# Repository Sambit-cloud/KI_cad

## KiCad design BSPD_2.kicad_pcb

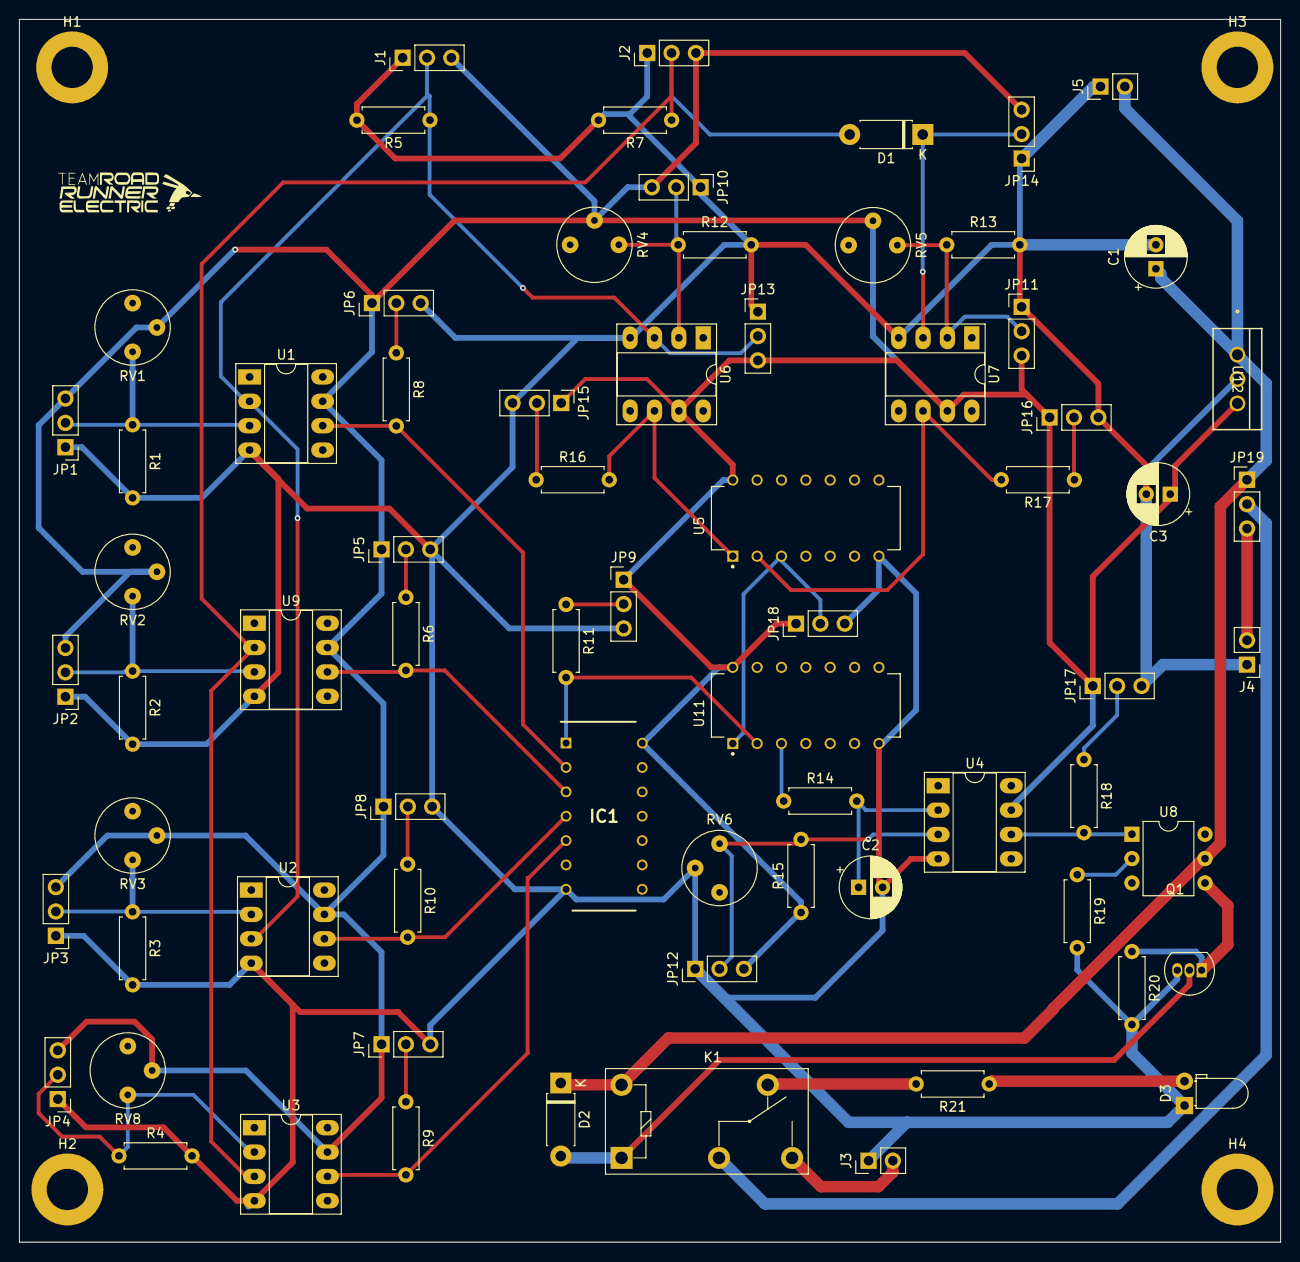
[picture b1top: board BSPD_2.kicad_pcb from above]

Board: 2 copper layers, 131.5 x 127.5 mm, 76 parts (0 on the bottom side), 40 nets.

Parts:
C1: 0.33u; CP_Radial_D6.3mm_P2.50mm
C2: 330u; CP_Radial_D6.3mm_P2.50mm
C3: 0.1u; CP_Radial_D6.3mm_P2.50mm
D1, D2: D; D_DO-41_SOD81_P7.62mm_Horizontal
D3: LED; LED_D3.0mm_Horizontal_O1.27mm_Z6.0mm
H1, H2, H3, H4: M4; MountingHole_4.3mm_M4_DIN965_Pad
IC1: CD4072BE; DIP794W53P254L1930H508Q14N
J1: BrakePressure_Sens_Input; PinHeader_1x03_P2.54mm_Vertical
J2: Current_Sensor_Input; PinHeader_1x03_P2.54mm_Vertical
J3: BSPD_Output; PinHeader_1x02_P2.54mm_Vertical
J4: Shutdown Line; PinHeader_1x02_P2.54mm_Vertical
J5: Voltage_Input; PinHeader_1x02_P2.54mm_Vertical
JP1, JP2, JP3, JP4, JP5, JP6, JP7, JP8, JP9, JP10, JP11, JP12, JP13, JP14, JP15, JP16, JP17, JP18, JP19: Jumper_3_Open; PinHeader_1x03_P2.54mm_Vertical
K1: G5Q-1; Relay_SPDT_Omron-G5Q-1
Q1: Q_NMOS_DGS; TO-92_Inline
R1, R14, R20: 1k; R_Axial_DIN0207_L6.3mm_D2.5mm_P7.62mm_Horizontal
R2, R4: 34k; R_Axial_DIN0207_L6.3mm_D2.5mm_P7.62mm_Horizontal
R3: 9k; R_Axial_DIN0207_L6.3mm_D2.5mm_P7.62mm_Horizontal
R5, R6, R7, R8, R9, R10, R11, R12, R13, R16, R17, R18: 10k; R_Axial_DIN0207_L6.3mm_D2.5mm_P7.62mm_Horizontal
R15: 47k; R_Axial_DIN0207_L6.3mm_D2.5mm_P7.62mm_Horizontal
R19: 249R; R_Axial_DIN0207_L6.3mm_D2.5mm_P7.62mm_Horizontal
R21: 500; R_Axial_DIN0207_L6.3mm_D2.5mm_P7.62mm_Horizontal
RV1, RV2, RV3, RV4, RV5, RV6, RV8: R_Potentiometer; Potentiometer_Bourns_3339P_Vertical_HandSoldering
U1, U2, U3, U4, U6, U7, U9: MCP6541; DIP-8_W7.62mm_Socket_LongPads
U5: SN74HC08NE4; DIP794W45P254L1969H508Q14
U8: 4N35; DIP-6_W7.62mm
U11: SN74HC32NE4; DIP794W45P254L1969H508Q14
U12: LM7805CT; TO220-3_ONS

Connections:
+5V: C3.1, IC1.14 (VDD), J1.3, J2.3, JP1.3 (B), JP2.3 (B), JP3.3 (B), JP4.3 (B), JP5.1 (A), JP6.1 (A), JP7.1 (A), JP8.1 (A), JP9.1 (A), JP10.3 (B), JP11.3 (B), JP12.3 (B), JP13.3 (B), JP14.3 (B), JP15.1 (A), JP16.1 (A), JP17.1 (A), JP18.1 (A), R15.1, RV1.2, RV2.2, RV3.2, RV4.2, RV5.2, RV8.2, U1.7 (V+), U2.7 (V+), U3.7 (V+), U4.7 (V+), U5.14 (VCC), U6.7 (V+), U7.7 (V+), U9.7 (V+), U11.14 (VCC), U12.3 (OUTPUT)
+12V: C1.1, D2.1 (K), J5.2, JP19.1 (A), K1.5, U8.5, U12.1 (INPUT)
/BSPD_Out: J3.2, K1.3
/BrakeSensIn: J1.2, JP13.2 (C), R5.1, U1.2 (-), U2.3 (+), U6.3 (+)
/CurrentSensIn: D1.2 (A), J2.2, R7.1, U3.3 (+), U9.2 (-)
/Fail_Check_Out: IC1.1 (J=A+B+C+D), R11.2, U11.2 (1B)
/SHD_Line: J4.2, JP19.3 (B)
/Trigger_Check_Out: JP18.2 (C), U5.3 (1Y), U11.1 (1A)
GND: C1.2, C2.2, C3.2, D3.1 (K), H1.1, H2.1, H3.1, H4.1, IC1.7 (VSS), J1.1, J2.1, J3.1, J4.1, J5.1, JP1.1 (A), JP2.1 (A), JP3.1 (A), JP4.1 (A), JP5.3 (B), JP6.3 (B), JP7.3 (B), JP8.3 (B), JP9.3 (B), JP10.1 (A), JP11.1 (A), JP12.1 (A), JP13.1 (A), JP14.1 (A), JP15.3 (B), JP16.3 (B), JP17.3 (B), JP18.3 (B), Q1.3 (S), R1.2, R2.2, R3.2, R4.2, R5.2, R7.2, R12.2, R13.2, R19.2, R20.2, RV6.2, U1.4 (V-), U2.4 (V-), U3.4 (V-), U4.4 (V-), U5.7 (GND), U6.4 (V-), U7.4 (V-), U9.4 (V-), U11.7 (GND), U12.2 (GND)
unnamed: D1.1 (K), JP14.2 (C), U7.3 (+)
unnamed: D2.2 (A), K1.1, Q1.2 (D)
unnamed: D3.2 (A), R21.1
unnamed: IC1.2 (A), R8.2, U1.6
unnamed: IC1.3 (B), R6.2, U9.6
unnamed: IC1.4 (C), R10.2, U2.6
unnamed: IC1.5 (D), R9.2, U3.6
unnamed: JP1.2 (C), R1.1, RV1.3, U1.3 (+)
unnamed: JP2.2 (C), R2.1, RV2.3, U9.3 (+)
unnamed: JP3.2 (C), R3.1, RV3.3, U2.2 (-)
unnamed: JP4.2 (C), R4.1, RV8.3, U3.2 (-)
unnamed: JP5.2 (C), R6.1
unnamed: JP6.2 (C), R8.1
unnamed: JP7.2 (C), R9.1
unnamed: JP8.2 (C), R10.1
unnamed: JP9.2 (C), R11.1
unnamed: JP10.2 (C), R12.1, RV4.3, U6.2 (-)
unnamed: JP11.2 (C), R13.1, RV5.3, U7.2 (-)
unnamed: JP12.2 (C), R15.2, RV6.3, U4.3 (+)
unnamed: JP15.2 (C), R16.1
unnamed: JP16.2 (C), R17.1
unnamed: JP17.2 (C), R18.1
unnamed: JP19.2 (C), K1.2
unnamed: K1.4, R21.2
unnamed: Q1.1 (G), R20.1, U8.4
unnamed: R18.2, U4.6, U8.1
unnamed: R19.1, U8.2
unnamed: C2.1, R14.2, U4.2 (-)
unnamed: R16.2, U5.1 (1A), U6.6
unnamed: R17.2, U5.2 (1B), U7.6
unnamed: R14.1, U11.3 (1Y)

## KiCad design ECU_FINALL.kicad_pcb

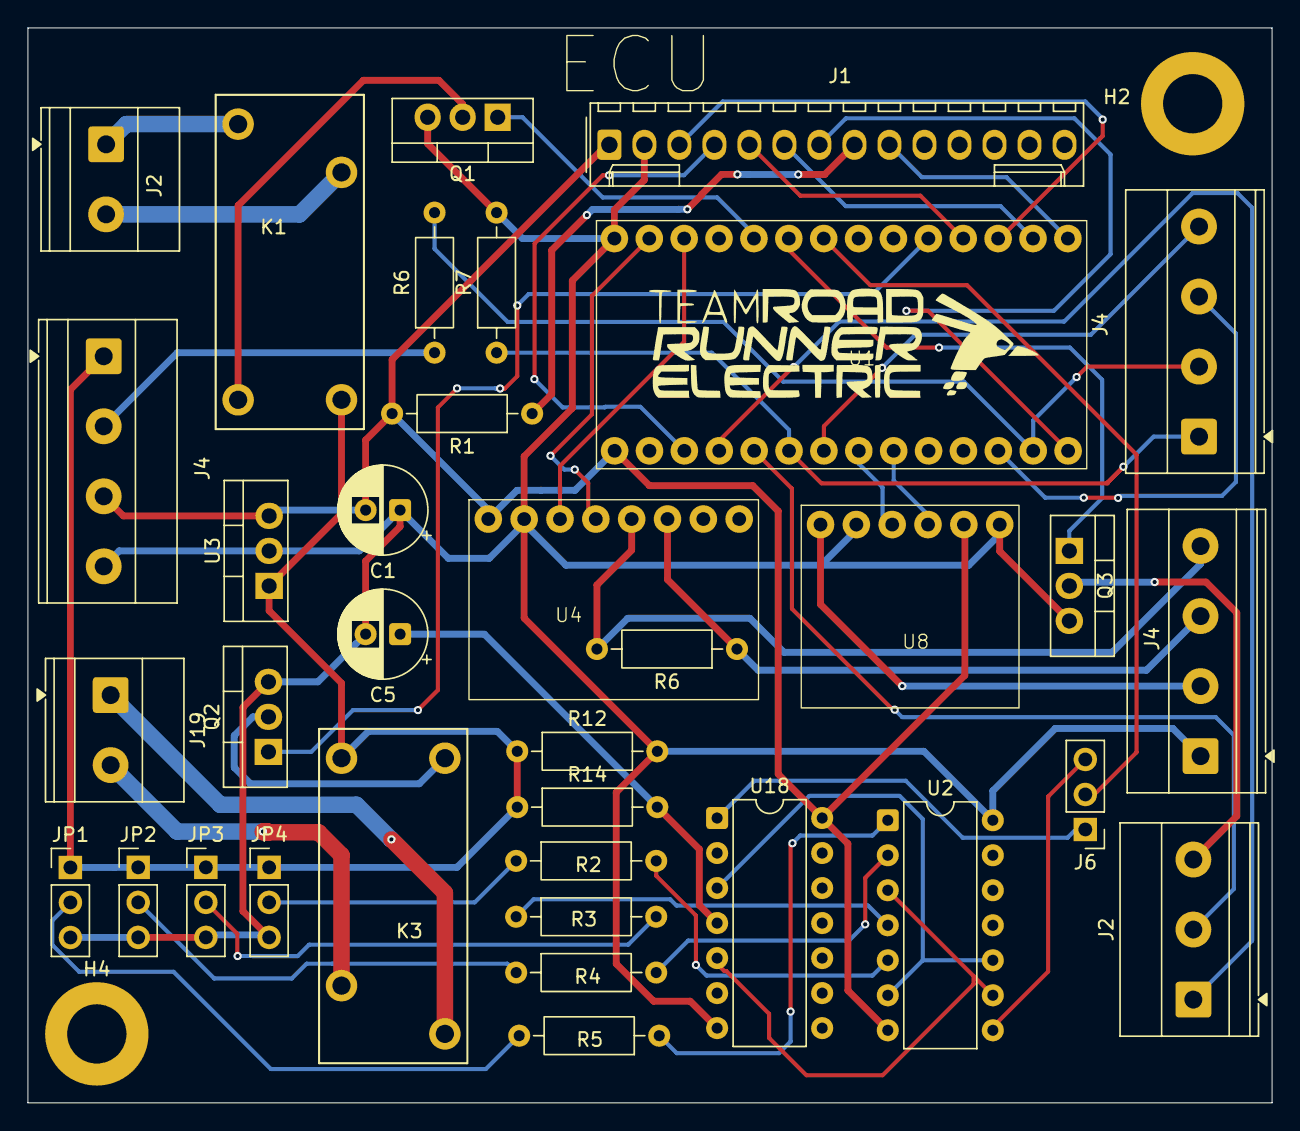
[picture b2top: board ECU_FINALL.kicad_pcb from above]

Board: 2 copper layers, 90.3 x 78.0 mm, 37 parts (0 on the bottom side), 48 nets.

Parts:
C1: 0.1uf; CP_Radial_D6.3mm_P2.50mm
C5: 10uF; CP_Radial_D6.3mm_P2.50mm
H2, H4: M4; MountingHole_4.3mm_M4_DIN965_Pad
J1: Conn_01x14_MountingPin; Molex_KK-254_AE-6410-14A_1x14_P2.54mm_Vertical
J2, J19: Screw_Terminal_01x02; TerminalBlock_Phoenix_MKDS-1,5-2-5.08_1x02_P5.08mm_Horizont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
J2#2: Screw_Terminal_01x02; TerminalBlock_Phoenix_MKDS-1,5-3-5.08_1x03_P5.08mm_Horizont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
J4, J4#2, J4#3: Screw_Terminal_01x04; TerminalBlock_Phoenix_MKDS-1,5-4-5.08_1x04_P5.08mm_Horizont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
J6: Conn_01x03_Pin; PinHeader_1x03_P2.54mm_Vertical
JP1, JP2, JP3, JP4: Jumper_3_Bridged12; PinHeader_1x03_P2.54mm_Vertical
K1, K3: G5PZ-1A_DC12; G5PZ_OMR
Q1, Q2, Q3: IRLZ44N; TO-220-3_Vertical
R1, R2, R3, R4, R5: R; R_Axial_DIN0207_L6.3mm_D2.5mm_P10.16mm_Horizontal
R6, R6#2, R7, R12, R14: 10k; R_Axial_DIN0207_L6.3mm_D2.5mm_P10.16mm_Horizontal
U1: Teensy4.0; teensy_holder
U2: 74LS08; DIP-14_W7.62mm
U3: LM7805_TO220; TO-220-3_Vertical
U4: TJA1051T; TJA1051T_THT
U8: MCP4725xxx-xCH; MCP4725_I2C_DAC_THT
U18: 4013; DIP-14_W7.62mm

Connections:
3.3V_IN: J4#2.2, R6.1
5V_Supply: C1.2, J1.1, J4#2.3, R1.2, U1.26 (VBAT), U2.7 (GND), U3.3 (VO), U4.1 (TXD), U8.5 (SCL), U18.14 (VDD)
12V_IN: J4#2.1, JP1.1 (A), JP2.1 (A), JP3.1 (A), JP4.1 (A), K1.1, K3.1, R12.1, R14.1, U3.1 (VI)
12V_MotorController: J2.2, K1.2
APPS1: J4#3.2, R6.2, U1.14 (20_A6_TX5_LRCLK1)
APPS2: J4#3.1, R7.1, U1.21 (13_SCK_CRX1_LED)
BUZZER_IN: Q3.1 (G), U1.6 (4_BCLK2)
BUZZER_OP: J2#2.3, Q3.2 (D)
CAN_HOut: J4.4, R6#2.2, U4.5 (NC)
CAN_LOut: J4.3, R6#2.1, U4.6 (CANL)
CAN_RX: U1.2 (0_RX1_CRX2_CS1), U4.4 (RXD)
CAN_TX: U1.3 (1_TX1_CTX2_MISO1), U4.3 (VCC)
GND: C1.1, C5.2, J1.2, J4.1, J4#2.4, JP1.3 (B), JP2.3 (B), JP3.3 (B), JP4.3 (B), Q1.3 (S), Q2.3 (S), Q3.3 (S), R7.2, R12.2, U1.1 (GND), U2.14 (VCC), U3.2 (GND), U4.2 (GND), U8.2 (VSS), U8.6 (A0), U18.7 (VSS)
MOTOR_RELAY: Q1.1 (G), U1.5 (3_LRCLK2)
unnamed: J1.3, U1.12 (10_CS_MQSR)
unnamed: J1.4, U1.24 (GND)
unnamed: J1.5, U1.11 (9_OUT1C)
unnamed: J1.6, U1.13 (11_MOSI_CTX1)
unnamed: J1.7, U1.13 (11_MOSI_CTX1)
unnamed: J1.8, R1.1
unnamed: J1.9, U1.14 (20_A6_TX5_LRCLK1)
unnamed: J6.1, U18.1 (Q)
unnamed: J6.3, U2.8
unnamed: JP1.2 (C), R5.2
unnamed: JP2.2 (C), R4.1
unnamed: JP3.2 (C), R3.2
unnamed: JP4.2 (C), R2.1
unnamed: K1.4, Q1.2 (D)
unnamed: K3.4, Q2.2 (D)
unnamed: U2.6, U2.10, U18.3 (C)
unnamed: U2.3, U2.9, U18.5 (D)
unnamed: C5.1, R14.2, U18.4 (R)
OUTPUT: J2.1, K1.3
PUSH _BUTTON: R3.1, U2.4
RTD_IN: J6.2, U1.7 (5_IN2)
SCL_I2C: U1.19 (15_A1_RX3_SPDIF_IN), U8.3 (VDD)
SDA_I2C: U1.18 (16_A2_RX4_SCL1), U8.4 (SDA)
SDIN/OUT_RELAY: Q2.1 (G), U1.10 (8_TX2_IN1)
SD_IN: J19.2, K3.2
SD_OUT: J19.1, K3.3
SHUTDOWN_BUTTON: R5.1, U2.1
SPEED: J2#2.1, U1.23 (PROGRAM)
START_BUTTON: R4.2, U2.2
SWITCH: R2.2, U2.5
TEMP1: J2#2.2, U1.22 (ON_OFF)
TEMP._SENS2: J4#3.4, U1.20 (14_A0_TX3_SPDIF_OUT)
TEMP._SENS3: J4#3.3, U1.15 (VBAT)
torque: J4.2, U8.1 (VOUT)

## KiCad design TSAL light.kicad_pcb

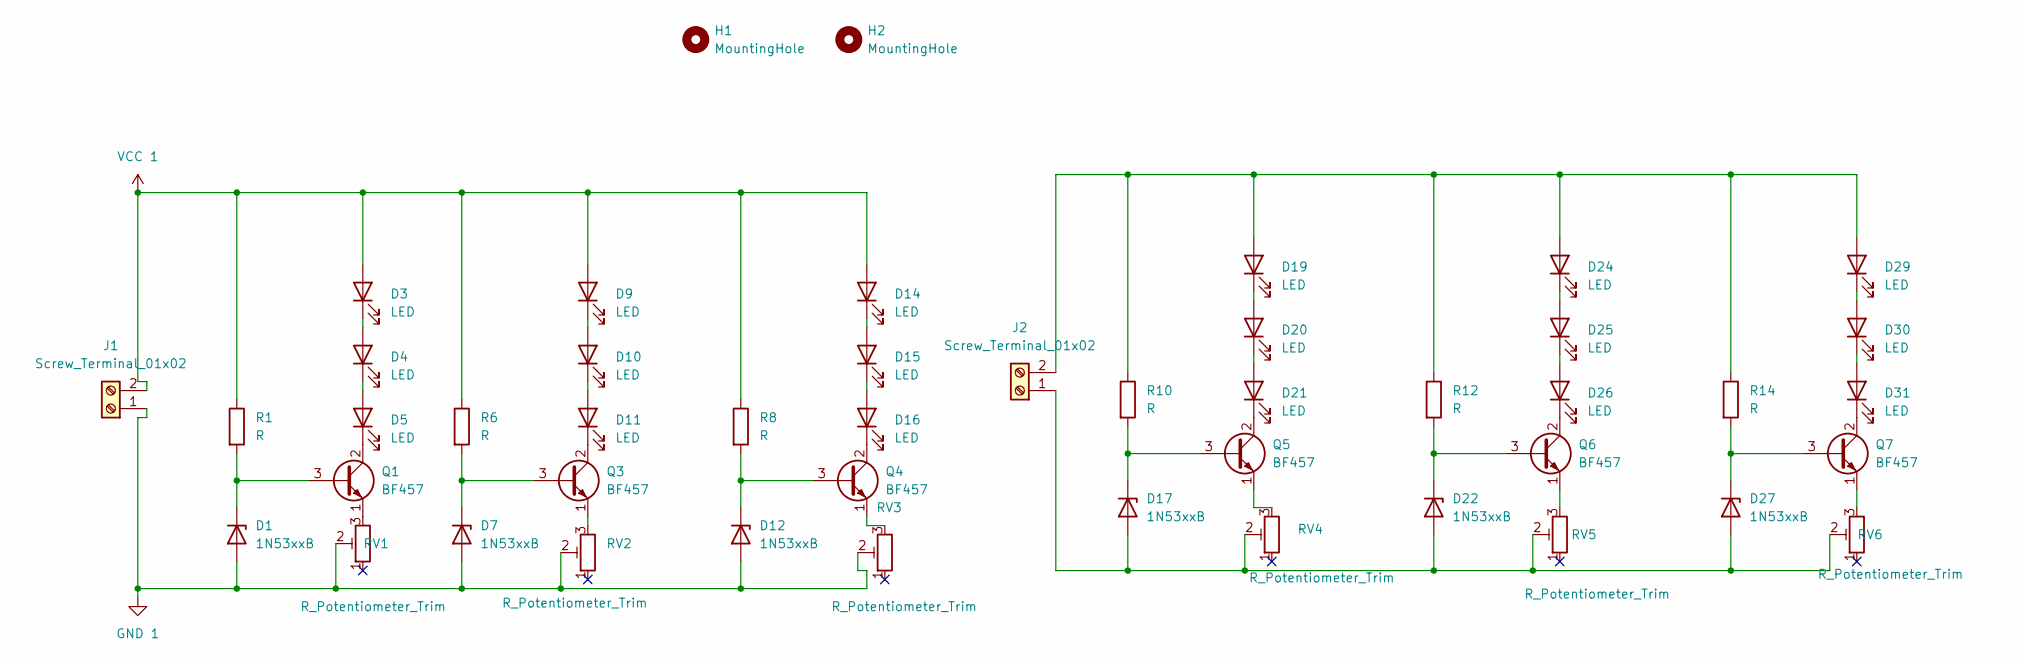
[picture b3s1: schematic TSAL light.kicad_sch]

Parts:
D1, D7, D12, D17, D22, D27: 1N53xxB; D_DO-35_SOD27_P7.62mm_Horizontal
D3, D4, D5, D9, D10, D11, D14, D15, D16, D19, D20, D21, D24, D25, D26, D29, D30, D31: LED; LED_D3.0mm_Clear
H1, H2: MountingHole; MountingHole_3.2mm_M3
J1, J2: Screw_Terminal_01x02; TerminalBlock_Phoenix_MKDS-1,5-2-5.08_1x02_P5.08mm_Horizont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
Q1, Q3, Q4, Q5, Q6, Q7: BF457; TO-92_Inline_Wide
R1, R6, R8, R10, R12, R14: R; R_Axial_DIN0204_L3.6mm_D1.6mm_P5.08mm_Horizontal
RV1, RV2, RV3, RV4, RV5, RV6: R_Potentiometer_Trim; Potentiometer_Vishay_T73YP_Vertical

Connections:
GND 1: D1.2 (A), D7.2 (A), D12.2 (A), J1.1, RV1.2, RV2.2, RV3.2
unnamed: D1.1 (K), Q1.3 (B), R1.2
unnamed: D3.1 (K), D4.2 (A)
unnamed: D4.1 (K), D5.2 (A)
unnamed: D5.1 (K), Q1.2 (C)
unnamed: D7.1 (K), Q3.3 (B), R6.2
unnamed: D9.1 (K), D10.2 (A)
unnamed: D10.1 (K), D11.2 (A)
unnamed: D11.1 (K), Q3.2 (C)
unnamed: D12.1 (K), Q4.3 (B), R8.2
unnamed: D14.1 (K), D15.2 (A)
unnamed: D15.1 (K), D16.2 (A)
unnamed: D16.1 (K), Q4.2 (C)
unnamed: D17.2 (A), D22.2 (A), D27.2 (A), J2.1, RV4.2, RV5.2, RV6.2
unnamed: D17.1 (K), Q5.3 (B), R10.2
unnamed: D19.2 (A), D24.2 (A), D29.2 (A), J2.2, R10.1, R12.1, R14.1
unnamed: D19.1 (K), D20.2 (A)
unnamed: D20.1 (K), D21.2 (A)
unnamed: D21.1 (K), Q5.2 (C)
unnamed: D22.1 (K), Q6.3 (B), R12.2
unnamed: D24.1 (K), D25.2 (A)
unnamed: D25.1 (K), D26.2 (A)
unnamed: D26.1 (K), Q6.2 (C)
unnamed: D27.1 (K), Q7.3 (B), R14.2
unnamed: D29.1 (K), D30.2 (A)
unnamed: D30.1 (K), D31.2 (A)
unnamed: D31.1 (K), Q7.2 (C)
unnamed: Q1.1 (E), RV1.3
unnamed: Q3.1 (E), RV2.3
unnamed: Q4.1 (E), RV3.3
unnamed: Q5.1 (E), RV4.3
unnamed: Q6.1 (E), RV5.3
unnamed: Q7.1 (E), RV6.3
VCC 1: D3.2 (A), D9.2 (A), D14.2 (A), J1.2, R1.1, R6.1, R8.1

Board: 2 copper layers, 46 parts (0 on the bottom side), 34 nets, no tracks yet.

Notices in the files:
parts and their libraries:
COPYRIGHT: Copyright (C) 2023 Ultra Librarian. All rights reserved.
